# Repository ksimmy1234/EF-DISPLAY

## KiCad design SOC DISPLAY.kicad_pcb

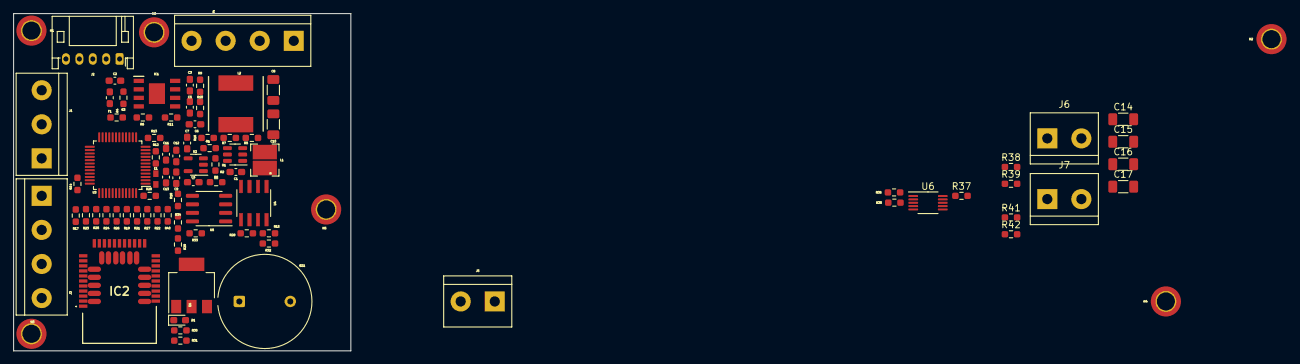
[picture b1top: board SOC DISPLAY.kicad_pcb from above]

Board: 2 copper layers, 50.3 x 50.3 mm, 87 parts (0 on the bottom side), 51 nets, no tracks yet.

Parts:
BZ1: Buzzer; Indicator_PUI_AI-1440-TWT-24V-2-R
C1: 0.1uf; C_0603_1608Metric_Pad1.08x0.95mm_HandSolder
C2: 2.2uF; C_0603_1608Metric_Pad1.08x0.95mm_HandSolder
C3: 2.2nf; C_0603_1608Metric_Pad1.08x0.95mm_HandSolder
C4: 1uf; C_0603_1608Metric_Pad1.08x0.95mm_HandSolder
C5: 56pF; C_0603_1608Metric_Pad1.08x0.95mm_HandSolder
C6: 2200pf; C_0603_1608Metric_Pad1.08x0.95mm_HandSolder
C7: 10nf; C_0603_1608Metric_Pad1.08x0.95mm_HandSolder
C8, C10: 22UF; C_1206_3216Metric_Pad1.33x1.80mm_HandSolder
C9: 2.2uf; C_0603_1608Metric_Pad1.08x0.95mm_HandSolder
C11: 1uF; C_0603_1608Metric_Pad1.08x0.95mm_HandSolder
C12, C13: 100nF; C_0603_1608Metric_Pad1.08x0.95mm_HandSolder
C14, C15, C16, C17: 22uF; C_1206_3216Metric_Pad1.33x1.80mm_HandSolder
D1: 5.6V; D_0603_1608Metric_Pad1.05x0.95mm_HandSolder
E1: LI0603G121R-10; FB_LI0603G121R-10
F1: Fuse; Fuse_0603_1608Metric_Pad1.05x0.95mm_HandSolder
H1, H2, H3, H4, H5, H6: Mount100VgHole; MountingHole_2.7mm_M2.5_ISO7380_Pad_TopBottom
IC1: LM5164QDDATQ1; SOIC127P600X170-9N
IC2: CM BLE
J1: PRG; TerminalBlock_bornier-3_P5.08mm
J2: Conn_01x05_Socket; JST_PH_S5B-PH-K_1x05_P2.00mm_Horizontal
J3, J4: OLED; TerminalBlock_bornier-4_P5.08mm
J5: Conn_01x02_Socket; TerminalBlock_bornier-2_P5.08mm
J6, J7: Conn_01x02_Pin; TerminalBlock_bornier-2_P5.08mm
L1: 3.3uH; INR33
L2: 100uH; 1267AY6R8NP3
Q1: NDT3055L; SOT-223-3_TabPin2
R1, R12, R14, R35, R36, R40, R41, R42: 10k; R_0603_1608Metric_Pad0.98x0.95mm_HandSolder
R2: 56k; R_0603_1608Metric_Pad0.98x0.95mm_HandSolder
R3: 1M; R_0603_1608Metric_Pad0.98x0.95mm_HandSolder
R4: 300K; R_0603_1608Metric_Pad0.98x0.95mm_HandSolder
R5, R7, R8, R15, R16, R17, R18, R27, R29, R32: 0R; R_0603_1608Metric_Pad0.98x0.95mm_HandSolder
R6: 100K; R_0603_1608Metric_Pad0.98x0.95mm_HandSolder
R9: 700k ohm; R_0603_1608Metric_Pad0.98x0.95mm_HandSolder
R10: 180k ohm; R_0603_1608Metric_Pad0.98x0.95mm_HandSolder
R11: 20k ohm; R_0603_1608Metric_Pad0.98x0.95mm_HandSolder
R13, R37, R39: 100R; R_0603_1608Metric_Pad0.98x0.95mm_HandSolder
R19, R20, R25, R26, R33: 100k; R_0603_1608Metric_Pad0.98x0.95mm_HandSolder
R21, R22, R23, R24, R31: 100E; R_0603_1608Metric_Pad0.98x0.95mm_HandSolder
R28, R34: 120R; R_0603_1608Metric_Pad0.98x0.95mm_HandSolder
R30: 3M; R_0603_1608Metric_Pad0.98x0.95mm_HandSolder
R38: 16.2M; R_0603_1608Metric_Pad0.98x0.95mm_HandSolder
U1: TPS563200; SOT-23-6
U2: LP2985-3.3; SOT-23-5
U3: STM32G0B1CBTx; LQFP-48_7x7mm_P0.5mm
U4: MAX485E; SOIC127P600X175-8N
U5: TJA1051T-3; SOIC-8_3.9x4.9mm_P1.27mm
U6: INA228AQDGSRQ1; VSSOP-10_3x3mm_P0.5mm

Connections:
3V3: C9.1, C11.1, C12.1, C13.1, C17.1, E1.1, E1.2, IC2.18 (3.3V_2), IC2.19 (3.3V_3), IC2.20 (3.3V_4), R12.1, R19.1, R20.1, R25.1, R26.1, R40.1, R41.1, R42.1, U2.5 (VOUT), U3.4 (VBAT), U3.5 (VREF+), U3.6 (VDD), U5.5 (VIO), U6.6 (VS)
5V: C4.1, J3.1, J4.1, R8.2, R15.1, R32.1, U2.1 (VIN), U2.3 (ON/~OFF), U4.8 (VCC), U5.3 (VCC)
5Vcc: L1.2, R2.2, R8.1
100V: C2.2, F1.2, IC1.2 (VIN), R3.1
/POWER_UNIT/12V: R5.2, R7.2, U1.3 (VIN), U1.5 (EN)
/POWER_UNIT/12Vcc: C6.2, C8.1, C10.1, L2.2, R5.1, R7.1, R10.1
/STM32MCU/NRST: R12.2, U3.10 (PF2)
/STM32MCU/RX: U3.34 (PA12/PA10), U4.1 (RO)
/STM32MCU/TX: U3.33 (PA11/PA9), U4.4 (DI)
A0: R35.1, U6.2 (A0)
A1: R36.1, U6.1 (A1)
ALERT: R41.2, U6.3 (ALERT)
GND: C4.2, C7.2, C8.2, C9.2, C10.2, C11.2, C12.2, C13.2, C14.2, C15.2, C17.2, D1.2 (A), IC1.9 (EP), IC2.11 (GND_1), IC2.21 (GND_4), IC2.22 (GND_5), IC2.23 (GND_6), IC2.24 (GND_7), IC2.25 (GND_8), IC2.26 (GND_9), IC2.28 (GND_10), IC2.30 (GND_12), IC2.32 (NC), J1.3, J2.4, J3.4, J4.4, J6.2, J7.1, Q1.3 (S), R1.1, R4.2, R6.2, R11.2, R14.2, R30.2, R33.2, R35.2, R36.2, U1.1 (GND), U2.2 (GND), U3.7 (VSS), U4.5 (GND), U5.2 (GND), U6.7 (GND)
H: R29.2, R34.2, U5.7 (CANH)
IN+: C16.1, R37.1, U6.10 (IN+)
IN-: C16.2, R39.1, U6.9 (IN-)
L: R18.2, R34.1, U5.6 (CANL)
unnamed: BZ1.2 (+), Q1.2 (D)
unnamed: BZ1.1 (-), R32.2
unnamed: C5.2, C6.1, R9.2
unnamed: D1.1 (K), Q1.1 (G), R30.1, R31.2
unnamed: C3.2, IC1.7 (BST)
unnamed: IC1.3 (EN/UVLO), R3.2, R4.1
unnamed: C5.1, IC1.5 (FB), R10.2, R11.1
unnamed: C2.1, IC1.1 (GND)
unnamed: IC1.4 (RON), R6.1
unnamed: C3.1, IC1.8 (SW), L2.1, R9.1
unnamed: F1.1, J2.1, R15.2, R16.2
unnamed: J2.2, R17.2, R18.1
unnamed: J2.3, R27.2, R29.1
unnamed: J5.1, R28.2, U4.7 (B)
unnamed: J5.2, R28.1, U4.6 (A)
unnamed: C7.1, U2.4 (BP)
unnamed: R13.1, U3.11 (PA0)
unnamed: R33.1, U5.8 (S)
PA3: J2.5, R13.2, R31.1
PACK+: C14.1, C15.1, J6.1, R37.2, R38.1, R38.2, U6.8 (VBUS)
PACK-: J7.2, R39.2
SCK: J4.3, R17.1, R21.1
SCK_2: J3.3, R23.1
SCL_PB3: R23.2, R25.2, U3.42 (PB3)
SCL_PB6: R19.2, R21.2, R42.2, U3.45 (PB6), U6.5 (SCL)
SDA1: J4.2, R22.1
SDA_2: J3.2, R24.1
SDA_PB4: R24.2, R26.2, U3.43 (PB4)
SDA_PB7: R20.2, R22.2, R27.1, R40.2, U3.46 (PB7), U6.4 (SDA)
SW2: C1.2, L1.1, U1.2 (SW)
SWCLK: IC2.2 (SWCLK), J1.1, R14.1, U3.36 (PA14)
SWDIO: IC2.1 (SWDIO), J1.2, U3.35 (PA13)
VBST: C1.1, U1.6 (VBST)
VFB: R1.2, R2.1, U1.4 (VFB)

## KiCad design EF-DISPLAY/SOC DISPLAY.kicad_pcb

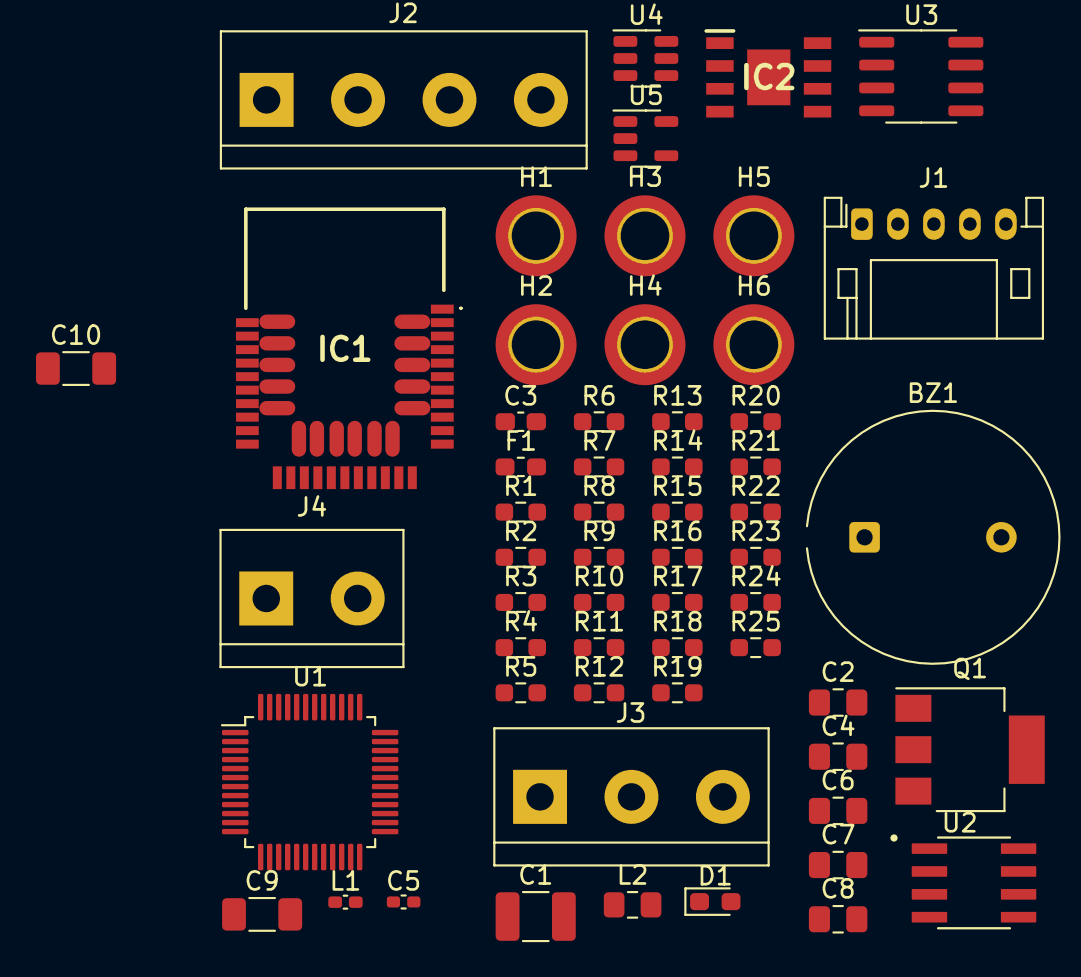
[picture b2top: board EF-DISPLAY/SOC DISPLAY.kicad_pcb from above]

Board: 2 copper layers, 58 parts (0 on the bottom side), 36 nets, no tracks yet.

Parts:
BZ1: Buzzer; Indicator_PUI_AI-1440-TWT-24V-2-R
C1: 2.2uf; C_1210_3225Metric_Pad1.33x2.70mm_HandSolder
C2, C4, C6, C8: 0.1uf; C_0805_2012Metric_Pad1.18x1.45mm_HandSolder
C3: 2.2nf; C_0603_1608Metric_Pad1.08x0.95mm_HandSolder
C5: 56pF; C_0402_1005Metric_Pad0.74x0.62mm_HandSolder
C7: 3.3nf; C_0805_2012Metric_Pad1.18x1.45mm_HandSolder
C9, C10: 22UF; C_1206_3216Metric_Pad1.33x1.80mm_HandSolder
D1: 5.6V; D_0603_1608Metric_Pad1.05x0.95mm_HandSolder
F1: Fuse; Fuse_0603_1608Metric_Pad1.05x0.95mm_HandSolder
H1, H2, H3, H4, H5, H6: Mount100VgHole; MountingHole_2.7mm_M2.5_ISO7380_Pad_TopBottom
IC1: CM BLE
IC2: LM5164QDDATQ1; SOIC127P600X170-9N
J1: Conn_01x05_Socket; JST_PH_S5B-PH-K_1x05_P2.00mm_Horizontal
J2: OLED; TerminalBlock_bornier-4_P5.08mm
J3: PRG; TerminalBlock_bornier-3_P5.08mm
J4: Conn_01x02_Socket; TerminalBlock_bornier-2_P5.08mm
L1: 3.3uH; L_0402_1005Metric_Pad0.77x0.64mm_HandSolder
L2: 68uH; L_0805_2012Metric_Pad1.15x1.40mm_HandSolder
Q1: NDT3055L; SOT-223-3_TabPin2
R1, R4, R19: 10k; R_0603_1608Metric_Pad0.98x0.95mm_HandSolder
R2: 1k; R_0603_1608Metric_Pad0.98x0.95mm_HandSolder
R3: 100R; R_0603_1608Metric_Pad0.98x0.95mm_HandSolder
R5: 3M; R_0603_1608Metric_Pad0.98x0.95mm_HandSolder
R6, R15, R16: 100E; R_0603_1608Metric_Pad0.98x0.95mm_HandSolder
R7, R8, R18: 100k; R_0603_1608Metric_Pad0.98x0.95mm_HandSolder
R9, R10, R11, R12, R13, R17: 0R; R_0603_1608Metric_Pad0.98x0.95mm_HandSolder
R14: 120R; R_0603_1608Metric_Pad0.98x0.95mm_HandSolder
R20: 100k ohm; R_0603_1608Metric_Pad0.98x0.95mm_HandSolder
R21: 56k; R_0603_1608Metric_Pad0.98x0.95mm_HandSolder
R22: 120k; R_0603_1608Metric_Pad0.98x0.95mm_HandSolder
R23, R24: 453k ohm; R_0603_1608Metric_Pad0.98x0.95mm_HandSolder
R25: 49.9k ohm; R_0603_1608Metric_Pad0.98x0.95mm_HandSolder
U1: STM32G0B1CBTx; LQFP-48_7x7mm_P0.5mm
U2: MAX485E; SOIC127P600X175-8N
U3: TJA1051T-3; SOIC-8_3.9x4.9mm_P1.27mm
U4: TPS563200; SOT-23-6
U5: LP2985-3.3; SOT-23-5

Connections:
5V: J2.1, L1.2, R10.1, R13.1, R21.2, U2.8 (VCC), U3.3 (VCC), U5.1 (VIN), U5.3 (ON/~OFF)
100V: C1.1, F1.2, IC2.2 (VIN), IC2.3 (EN/UVLO)
/3V3: C4.2, C6.2, C8.1, IC1.18 (3.3V_2), IC1.19 (3.3V_3), IC1.20 (3.3V_4), R1.1, R7.1, R8.1, U1.4 (VBAT), U1.5 (VREF+), U1.6 (VDD), U3.5 (VIO), U5.5 (VOUT)
/12V: C7.2, C9.1, C10.1, L2.2, R24.1, U4.3 (VIN), U4.5 (EN)
/NRST: R1.2, U1.10 (PF2)
/RST: IC1.3 (P21/RST), U1.47 (PB8)
/RX: R2.1, U1.34 (PA12/PA10), U2.1 (RO), U3.4 (RXD)
/TX: IC1.9 (P12), IC1.10, R2.2, U1.33 (PA11/PA9), U2.4 (DI), U3.1 (TXD)
GND: C1.2, C4.1, C6.1, C8.2, C9.2, C10.2, D1.2 (A), IC1.11 (GND_1), IC1.21 (GND_4), IC1.22 (GND_5), IC1.23 (GND_6), IC1.24 (GND_7), IC1.25 (GND_8), IC1.26 (GND_9), IC1.28 (GND_10), IC1.30 (GND_12), IC1.32 (NC), IC2.1 (GND), J1.4, J2.4, J3.3, Q1.3 (S), R4.2, R5.2, R18.2, R19.1, R20.2, R25.2, U1.7 (VSS), U2.5 (GND), U3.2 (GND), U4.1 (GND), U5.2 (GND)
H: R17.2, R22.2, U3.7 (CANH)
L: R12.2, R22.1, U3.6 (CANL)
unnamed: BZ1.2 (+), Q1.2 (D)
unnamed: BZ1.1 (-), R10.2
unnamed: C5.2, C7.1, R23.2
unnamed: D1.1 (K), Q1.1 (G), R5.1, R6.2
unnamed: C3.2, IC2.7 (BST)
unnamed: C5.1, IC2.5 (FB), R24.2, R25.1
unnamed: IC2.4 (RON), R20.1
unnamed: C3.1, IC2.8 (SW), L2.1, R23.1
unnamed: F1.1, J1.1, R9.2
unnamed: J1.2, R11.2, R12.1
unnamed: J1.3, R13.2, R17.1
unnamed: J4.1, R14.2, U2.7 (B)
unnamed: J4.2, R14.1, U2.6 (A)
unnamed: R3.1, U1.11 (PA0)
unnamed: R18.1, U3.8 (S)
PA3: J1.5, R3.2, R6.1
SCK: J2.3, R11.1, R15.1
SCL: R7.2, R15.2, U1.45 (PB6)
SDA: R8.2, R9.1, R16.2, U1.46 (PB7)
SDA1: J2.2, R16.1
SW2: C2.2, L1.1, U4.2 (SW)
SWCLK: IC1.2 (SWCLK), J3.1, R4.1, U1.36 (PA14)
SWDIO: IC1.1 (SWDIO), J3.2, U1.35 (PA13)
VBST: C2.1, U4.6 (VBST)
VFB: R19.2, R21.1, U4.4 (VFB)

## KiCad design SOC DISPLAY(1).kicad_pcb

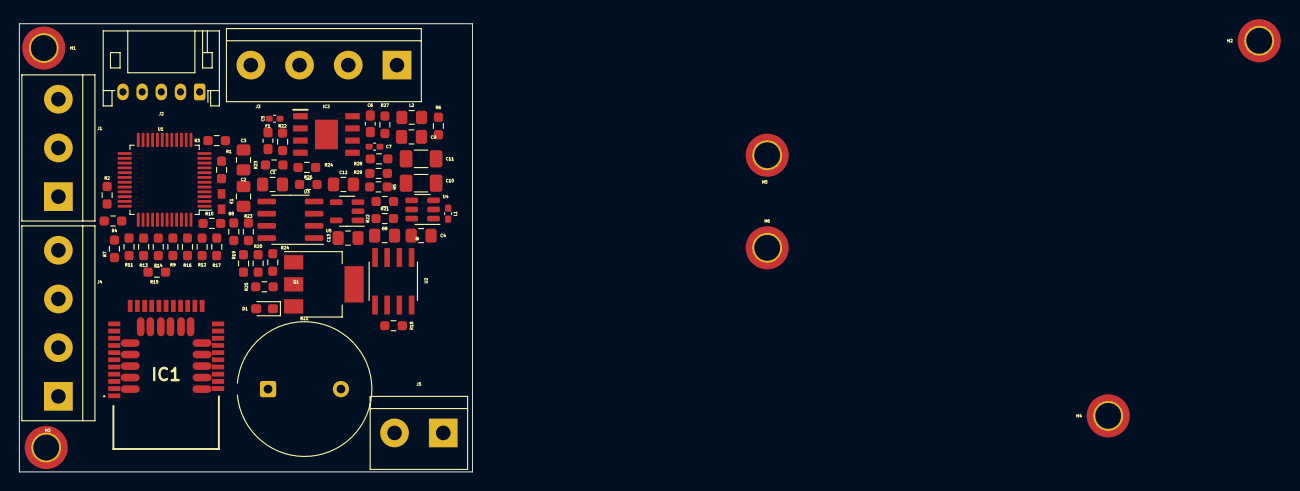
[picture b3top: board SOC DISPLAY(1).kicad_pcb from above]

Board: 2 copper layers, 47.2 x 46.7 mm, 70 parts (0 on the bottom side), 42 nets.

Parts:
BZ1: Buzzer; Indicator_PUI_AI-1440-TWT-24V-2-R
C1: 1uF; C_0805_2012Metric_Pad1.18x1.45mm_HandSolder
C2, C3: 100nF; C_0805_2012Metric_Pad1.18x1.45mm_HandSolder
C4: 0.1uf; C_0805_2012Metric_Pad1.18x1.45mm_HandSolder
C5: 2.2uF; C_0402_1005Metric_Pad0.74x0.62mm_HandSolder
C6: 2.2nf; C_0603_1608Metric_Pad1.08x0.95mm_HandSolder
C7: 56pF; C_0402_1005Metric_Pad0.74x0.62mm_HandSolder
C8: 1uf; C_0805_2012Metric_Pad1.18x1.45mm_HandSolder
C9: 2200pf; C_0805_2012Metric_Pad1.18x1.45mm_HandSolder
C10, C11: 22UF; C_1206_3216Metric_Pad1.33x1.80mm_HandSolder
C12: 10nf; C_0805_2012Metric_Pad1.18x1.45mm_HandSolder
C13: 2.2uf; C_0805_2012Metric_Pad1.18x1.45mm_HandSolder
D1: 5.6V; D_0603_1608Metric_Pad1.05x0.95mm_HandSolder
E1: LI0603G121R-10; FB_LI0603G121R-10
F1: Fuse; Fuse_0603_1608Metric_Pad1.05x0.95mm_HandSolder
H1, H2, H3, H4, H5, H6: Mount100VgHole; MountingHole_2.7mm_M2.5_ISO7380_Pad_TopBottom
IC1: CM BLE
IC2: LM5164QDDATQ1; SOIC127P600X170-9N
J1: PRG; TerminalBlock_bornier-3_P5.08mm
J2: Conn_01x05_Socket; JST_PH_S5B-PH-K_1x05_P2.00mm_Horizontal
J3, J4: OLED; TerminalBlock_bornier-4_P5.08mm
J5: Conn_01x02_Socket; TerminalBlock_bornier-2_P5.08mm
L1: 3.3uH; L_0402_1005Metric_Pad0.77x0.64mm_HandSolder
L2: 100uH; L_0805_2012Metric_Pad1.15x1.40mm_HandSolder
Q1: NDT3055L; SOT-223-3_TabPin2
R1, R4, R21: 10k; R_0603_1608Metric_Pad0.98x0.95mm_HandSolder
R2: 1k; R_0603_1608Metric_Pad0.98x0.95mm_HandSolder
R3: 100R; R_0603_1608Metric_Pad0.98x0.95mm_HandSolder
R5, R6, R7, R8, R17, R19, R26: 0R; R_0603_1608Metric_Pad0.98x0.95mm_HandSolder
R9, R10, R13, R14, R20: 100k; R_0603_1608Metric_Pad0.98x0.95mm_HandSolder
R11, R12, R15, R16, R25: 100E; R_0603_1608Metric_Pad0.98x0.95mm_HandSolder
R18, R23: 120R; R_0603_1608Metric_Pad0.98x0.95mm_HandSolder
R22: 56k; R_0603_1608Metric_Pad0.98x0.95mm_HandSolder
R22#2: 1M1; R_0603_1608Metric_Pad0.98x0.95mm_HandSolder
R23#2: 332K; R_0603_1608Metric_Pad0.98x0.95mm_HandSolder
R24: 3M; R_0603_1608Metric_Pad0.98x0.95mm_HandSolder
R24#2: 100K; R_0603_1608Metric_Pad0.98x0.95mm_HandSolder
R27: 698k ohm; R_0603_1608Metric_Pad0.98x0.95mm_HandSolder
R28: 180k ohm; R_0603_1608Metric_Pad0.98x0.95mm_HandSolder
R29: 20k ohm; R_0603_1608Metric_Pad0.98x0.95mm_HandSolder
U1: STM32G0B1CBTx; LQFP-48_7x7mm_P0.5mm
U2: MAX485E; SOIC127P600X175-8N
U3: TJA1051T-3; SOIC-8_3.9x4.9mm_P1.27mm
U4: TPS563200; SOT-23-6
U5: LP2985-3.3; SOT-23-5

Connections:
5V: C8.1, J3.1, J4.1, L1.2, R5.1, R22.2, R26.1, U2.8 (VCC), U3.3 (VCC), U5.1 (VIN), U5.3 (ON/~OFF)
100V: C5.2, F1.2, IC2.2 (VIN), R22#2.1
/3V3: C1.1, C2.1, C3.1, C13.1, E1.1, E1.2, IC1.18 (3.3V_2), IC1.19 (3.3V_3), IC1.20 (3.3V_4), R1.1, R9.1, R10.1, R13.1, R14.1, U1.4 (VBAT), U1.5 (VREF+), U1.6 (VDD), U3.5 (VIO), U5.5 (VOUT)
/12V: C9.2, C10.1, C11.1, L2.2, R6.1, R28.1, U4.3 (VIN), U4.5 (EN)
/NRST: R1.2, U1.10 (PF2)
/RST: IC1.3 (P21/RST), U1.47 (PB8)
/RX: R2.1, U1.34 (PA12/PA10), U2.1 (RO), U3.4 (RXD)
/TX: IC1.9 (P12), IC1.10, R2.2, U1.33 (PA11/PA9), U2.4 (DI), U3.1 (TXD)
GND: C1.2, C2.2, C3.2, C8.2, C10.2, C11.2, C12.2, C13.2, D1.2 (A), IC1.11 (GND_1), IC1.21 (GND_4), IC1.22 (GND_5), IC1.23 (GND_6), IC1.24 (GND_7), IC1.25 (GND_8), IC1.26 (GND_9), IC1.28 (GND_10), IC1.30 (GND_12), IC1.32 (NC), J1.3, J2.4, J3.4, J4.4, Q1.3 (S), R4.2, R20.2, R21.1, R23#2.2, R24.2, R24#2.2, R29.2, U1.7 (VSS), U2.5 (GND), U3.2 (GND), U4.1 (GND), U5.2 (GND)
H: R19.2, R23.2, U3.7 (CANH)
L: R8.2, R23.1, U3.6 (CANL)
unnamed: BZ1.2 (+), Q1.2 (D)
unnamed: BZ1.1 (-), R26.2
unnamed: C7.2, C9.1, R27.2
unnamed: D1.1 (K), Q1.1 (G), R24.1, R25.2
unnamed: C6.2, IC2.7 (BST)
unnamed: IC2.3 (EN/UVLO), R22#2.2, R23#2.1
unnamed: C7.1, IC2.5 (FB), R28.2, R29.1
unnamed: C5.1, IC2.1 (GND)
unnamed: IC2.4 (RON), R24#2.1
unnamed: C6.1, IC2.8 (SW), L2.1, R27.1
unnamed: F1.1, J2.1, R5.2, R6.2
unnamed: J2.2, R7.2, R8.1
unnamed: J2.3, R17.2, R19.1
unnamed: J5.1, R18.2, U2.7 (B)
unnamed: J5.2, R18.1, U2.6 (A)
unnamed: R3.1, U1.11 (PA0)
unnamed: R20.1, U3.8 (S)
unnamed: C12.1, U5.4 (BP)
PA3: J2.5, R3.2, R25.1
SCK: J4.3, R7.1, R15.1
SCK_2: J3.3, R11.1
SCL_PB6: R9.2, R15.2, U1.45 (PB6)
SDA1: J4.2, R16.1
SDA_2: J3.2, R12.1
SDA_PB4: R14.2, U1.43 (PB4)
SDA_PB7: R10.2, R12.2, R16.2, R17.1, U1.46 (PB7)
SW2: C4.2, L1.1, U4.2 (SW)
SWCLK: IC1.2 (SWCLK), J1.1, R4.1, U1.36 (PA14)
SWDIO: IC1.1 (SWDIO), J1.2, U1.35 (PA13)
VBST: C4.1, U4.6 (VBST)
VFB: R21.2, R22.1, U4.4 (VFB)

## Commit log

2023-07-27 2nd Commit
2023-07-27 new change
2023-07-28 Schematic Change
2023-07-30 chanses made
2023-07-31 placing
2023-08-03 Sch Changes
2023-08-04 frst
2023-08-04 Matic
2023-08-04 chull
2023-08-04 Done
2023-08-04 Designator
2023-08-04 NAYE
2023-08-05 Placing Soc
2023-08-05 add text
2023-08-05 some
2023-08-07 make connection between stm and ina and add connectors
2023-08-07 giga
2023-08-09 buck
2023-08-10 pull
